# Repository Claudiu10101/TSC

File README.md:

## 1. Descrierea Detaliată a Funcționalității Hardware

Sistemul este un ceas inteligent (smartwatch) cu consum ultra-redus de energie, bazat pe SoC-ul **nRF52840**, care integrează conectivitate Bluetooth Low Energy (BLE) și un afișaj de tip E-Paper (E-Ink).

### Module și Componente Cheie:
* **Unitatea Centrală (MCU):** **nRF52840** (Cortex-M4F la 64MHz). Este ales pentru suportul hardware de Floating Point (necesar procesării datelor de la senzori) și pentru managementul avansat al energiei.
* **Afișajul (E-Paper):** Spre deosebire de ecranele LCD/OLED, acesta consumă energie **doar la schimbarea imaginii**. Circuitul de control (E-Paper Drive) utilizează un convertor boost format din inductorul **L5 (68µH)** și diodele **MBR0530** pentru a genera tensiunile de ±15V necesare orientării particulelor de pigment din ecran.
* **Managementul Bateriei (Power Management):**
    * **Charger (BQ25180):** Permite încărcarea controlată prin USB și monitorizarea prin I2C.
    * **Fuel Gauge (MAX17048):** Folosește algoritmul *ModelGauge* pentru a estima procentul bateriei fără a necesita un rezistor de descărcare (shunt), economisind energie.
    * **Regulator Buck-Boost (RT6160):** Menține constantă tensiunea de 3.3V chiar și când bateria scade sub acest prag (până la 2.5V), maximizând timpul de utilizare.
* **Senzori și Feedback:**
    * **Accelerometru (BMA423):** Include funcții hardware pentru numărarea pașilor (pedometer) și detectarea gestului de "ridicare mână" (tilt-to-wake), trimițând o întrerupere către MCU pentru a-l trezi din sleep.
    * **Haptic Driver (DRV2605):** Permite generarea de efecte de vibrație complexe (peste 100 de librării incluse) pentru notificări discrete.

### Specificații de Comunicație:
* **I2C (Inter-Integrated Circuit):** Lucrează la 400kHz (Fast Mode). Conectează Charger-ul, Fuel Gauge-ul, IMU-ul și Haptic Driver-ul. Această magistrală este ideală pentru senzori datorită simplității și consumului redus.
* **SPI (Serial Peripheral Interface):** Folosit exclusiv pentru ecranul E-Paper pentru a asigura o rată de transfer a datelor suficient de mare pentru refresh-ul imaginii.

---

## 2. Diagrama bloc

```mermaid
graph TD
    %% -- Nodul Central (Microcontroller) --
    subgraph MCU_Block ["Nucleu Central"]
        nRF52840["nRF52840 SoC (Bluetooth 5 / RF)"]
    end

    %% -- Modulul Power Management --
    subgraph Power_Block ["Management Alimentare"]
        LiPo_Batt(("Baterie LiPo 3.7V"))
        USBC_Conn["Conector USB-C (Alimentare/Date)"]
        Charger_BQ["BQ25180 Charger IC"]
        Fuel_MAX["MAX17048 Fuel Gauge"]
        Reg_RT["RT6160 Buck-Boost Regulator"]
    end

    %% -- Modulul Afișaj --
    subgraph Display_Block ["Interfață Vizuală"]
        FPC_Conn["Conector FPC 24p"]
        EPD_Driver["Circuit Comandă E-Paper"]
        EPD_Screen["Ecran E-Paper (E-Ink)"]
    end

    %% -- Modulul Senzori & Feedback --
    subgraph Sensor_Feedback_Block ["Senzori și Actuatori"]
        IMU_BMA["BMA423 Accelerometru"]
        Haptic_DRV["DRV2605 Haptic Driver"]
        Haptic_Mot(("Motor Vibrații"))
    end

    %% -- Linii de Alimentare --
    USBC_Conn ==> Charger_BQ
    LiPo_Batt <==> Charger_BQ
    LiPo_Batt -.-> Fuel_MAX
    Charger_BQ ==> Reg_RT
    Reg_RT ==> nRF52840
    Reg_RT ==> IMU_BMA
    Reg_RT ==> FPC_Conn
    Reg_RT ==> Haptic_DRV

    %% -- Linii de Date --
    nRF52840 <-->|I2C| Charger_BQ
    nRF52840 <-->|I2C| Fuel_MAX
    nRF52840 <-->|I2C| IMU_BMA
    nRF52840 <-->|I2C| Haptic_DRV
    nRF52840 -->|SPI| FPC_Conn
    FPC_Conn <--> EPD_Driver
    EPD_Driver ==> EPD_Screen
```

## 3. Configurarea Pinilor nRF52840 (Pinout Mapping)

Alegerea pinilor pe nRF52840 este critică pentru a evita interferențele și pentru a optimiza rutarea semnalelor RF.

| Pin MCU | Funcție Schematic | Explicație și Justificare |
| :--- | :--- | :--- |
| **P0.26 / P0.27** | **SDA / SCL** | **Magistrala I2C.** Sunt pini digitali generali. S-au ales acești pini pentru a păstra magistrala de senzori grupată fizic pe PCB. |
| **P1.01** | **EPD_BUSY** | **Intrare digitală.** MCU citește acest pin pentru a ști când ecranul a terminat operațiunea de refresh (activ high). |
| **P1.02** | **EPD_RES** | **Reset ecran.** Pin digital folosit pentru inițializarea hardware a controlerului de display. |
| **P1.03** | **EPD_DC** | **Data/Command.** Semnal de control SPI care indică dacă datele trimise sunt comenzi sau pixeli. |
| **P1.04** | **EPD_CS** | **Chip Select.** Activează comunicația SPI cu ecranul. |
| **P1.05** | **EPD_SCK** | **SPI Clock.** Generat de MCU pentru sincronizarea datelor către ecran. |
| **P1.06** | **EPD_MOSI** | **Master Out Slave In.** Linia principală de date către afișaj. |
| **P0.11** | **INT_IMU** | **Intrare Întrerupere.** Conectat la pinul INT1 al BMA423. Trezește procesorul din modul System OFF la detectarea mișcării. |
| **P0.03** | **HAPTIC_EN** | **Trigger.** Activează driverul de vibrații. Poate fi folosit și cu PWM pentru intensitate variabilă. |
| **P0.02, P0.29, P0.31** | **Buttons (UP, ENT, DN)** | **Interfață Utilizator.** Configurați cu Pull-Up intern. Sunt pini capabili de "Sense" pentru a trezi dispozitivul din moduri de consum ultra-redus. |

### Calcule și Considerente de Consum:
1.  **Mod Sleep (Deep Sleep):** Cu nRF52840 în modul *System ON Idle* și senzorii în mod *Low Power*, consumul estimat este de aproximativ **15-20 µA**.
2.  **Refresh Ecran:** În timpul celor 1-2 secunde de refresh E-Paper, consumul sare la **5-10 mA** datorită convertorului boost.
3.  **Baterie:** Folosind o baterie LiPo de 100mAh, cu un management corect al sleep-ului, autonomia poate depăși **2-3 săptămâni**.

Acest design respectă rigurozitatea cerută în cadrul cursului TSC, punând accent pe utilizarea eficientă a perifericelor hardware ale nRF52840 și pe independența modulelor față de CPU prin utilizarea întreruperilor.

### 4. Bill of materials

| Cantitate | Componentă / Modul | Designator (Parts) | Descriere Scurtă | Link Achiziție / Resurse | Datasheet / Link Producător |
| :--- | :--- | :--- | :--- | :--- | :--- |
| 1 | **nRF52840** | U$1 | [cite_start]Microcontroler Bluetooth [cite: 738, 740] | [Mouser/Search](https://www.mouser.com) | [Nordic Semi](https://www.google.com/search?q=https://www.nordicsemi.com) |
| 1 | **2450AT18B100E** | ANT1 | [cite_start]Antenă Chip 2.45GHz [cite: 358, 360] | [cite_start][Arrow Link](https://www.arrow.com/en/products/2450at18b100e/johanson-dielectrics) [cite: 360] | [cite_start][Johanson Tech](https://www.google.com/search?q=https://www.mouser.co.uk/ProductDetail/Johanson-Technology/2450at18b100e) [cite: 364] |
| 1 | **BQ25180YBGR** | IC1 | [cite_start]Charger IC Li-Ion/Polymer [cite: 574, 576] | [cite_start][Mouser Link](https://www.google.com/search?q=https://www.mouser.co.uk/ProductDetail/Texas-Instruments/BQ25180YBGR) [cite: 581] | [cite_start][Texas Instruments](https://www.google.com/search?q=https://www.arrow.com/en/products/bq25180ybgr/texas-instruments) [cite: 576] |
| 1 | **RT6160AWSC** | IC2 | [cite_start]Buck-Boost Regulator [cite: 755, 757] | [cite_start][Mouser Link](https://www.google.com/search?q=https://www.mouser.co.uk/ProductDetail/Richtek/RT6160AWSC) [cite: 762] | [cite_start][Richtek](https://www.google.com/search?q=https://www.mouser.co.uk/ProductDetail/Richtek/RT6160AWSC) [cite: 762] |
| 1 | **BMA423** | IC3 | [cite_start]Accelerometru 3 axe [cite: 559, 561] | [cite_start][Mouser Link](https://www.google.com/search?q=https://www.mouser.co.uk/ProductDetail/Bosch-Sensortec/BMA423) [cite: 566] | [cite_start][Bosch Sensortec](https://www.arrow.com/en/products/bma423/bosch) [cite: 562] |
| 1 | **DRV2605YZFR** | IC4 | [cite_start]Haptic Driver (ERM/LRA) [cite: 604, 606] | [cite_start][Arrow Link](https://www.arrow.com/en/products/drv2605yzfr/texas-instruments) [cite: 606] | [cite_start][Texas Instruments](https://www.arrow.com/en/products/drv2605yzfr/texas-instruments) [cite: 606] |
| 1 | **FTC252012SR47MBCA** | L1 | [cite_start]Inductor 0.47µH [cite: 706, 707] | [cite_start][**JLC Parts (C5832368)**](https://jlcpcb.com/partdetail/6763488-FTC252012SR47MBCA/C5832368) [cite: 712] | [cite_start][TDK](https://jlcpcb.com/partdetail/6763488-FTC252012SR47MBCA/C5832368) [cite: 712] |
| 1 | **KH-TYPE-C-16P** | J2 | [cite_start]Conector USB-C 16 pini [cite: 691, 692] | [cite_start][SnapEDA Link](https://www.snapeda.com/parts/KH-TYPE-C-16P/Kinghelm/view-part/?ref=snap) [cite: 703] | [cite_start][Kinghelm](https://www.snapeda.com/parts/KH-TYPE-C-16P/Kinghelm/view-part/?ref=eda) [cite: 694] |
| 1 | **503480-2400** | J1 | [cite_start]Conector FPC 24 pini [cite: 493, 494] | [cite_start][Mouser Link](https://www.google.com/search?q=https://www.mouser.co.uk/ProductDetail/Molex/503480-2400) [cite: 500] | [cite_start][Molex](https://www.google.com/search?q=https://www.mouser.co.uk/ProductDetail/Molex/503480-2400) [cite: 500] |
| 3 | **MBR0530** | D1, D2, D3 | [cite_start]Diodă Schottky 0.5A 30V [cite: 632, 634] | [cite_start][SnapEDA Link](https://www.snapeda.com/parts/MBR0530/Onsemi/view-part/?ref=snap) [cite: 642] | [cite_start][ON Semi](https://www.snapeda.com/parts/MBR0530/Onsemi/view-part/?ref=eda) [cite: 636] |
| 1 | **USBLC6-2SC6Y** | D4 | [cite_start]Protecție ESD SOT-23-6 [cite: 619, 621] | [cite_start][SnapEDA Link](https://www.snapeda.com/parts/USBLC6-2SC6Y/STMicroelectronics/view-part/?ref=snap) [cite: 629] | [cite_start][STMicro](https://www.snapeda.com/parts/USBLC6-2SC6Y/STMicroelectronics/view-part/?ref=eda) [cite: 622] |
| 1 | **SI1308EDL-T1-GE3** | Q1 | [cite_start]MOSFET N-Ch 30V 1.5A [cite: 646, 647] | [cite_start][SnapEDA Link](https://www.snapeda.com/parts/SI1308EDL-T1-GE3/Vishay+Siliconix/view-part/?ref=snap) [cite: 656] | [cite_start][Vishay](https://www.snapeda.com/parts/SI1308EDL-T1-GE3/Vishay+Siliconix/view-part/?ref=eda) [cite: 648] |
| 3 | **EVP-AKE31A** | SW1-SW3 | [cite_start]Întrerupător (Switch) [cite: 326, 327] | [Panasonic Search](https://www.mouser.com) | [Panasonic](https://www.mouser.com) |
| 1 | **TC2030-IDC** | J3 | [cite_start]Adaptor programare 6 pini [cite: 770, 771] | [Tag-Connect](https://www.tag-connect.com) | [cite_start][Tag-Connect](https://www.tag-connect.com) [cite: 776] |

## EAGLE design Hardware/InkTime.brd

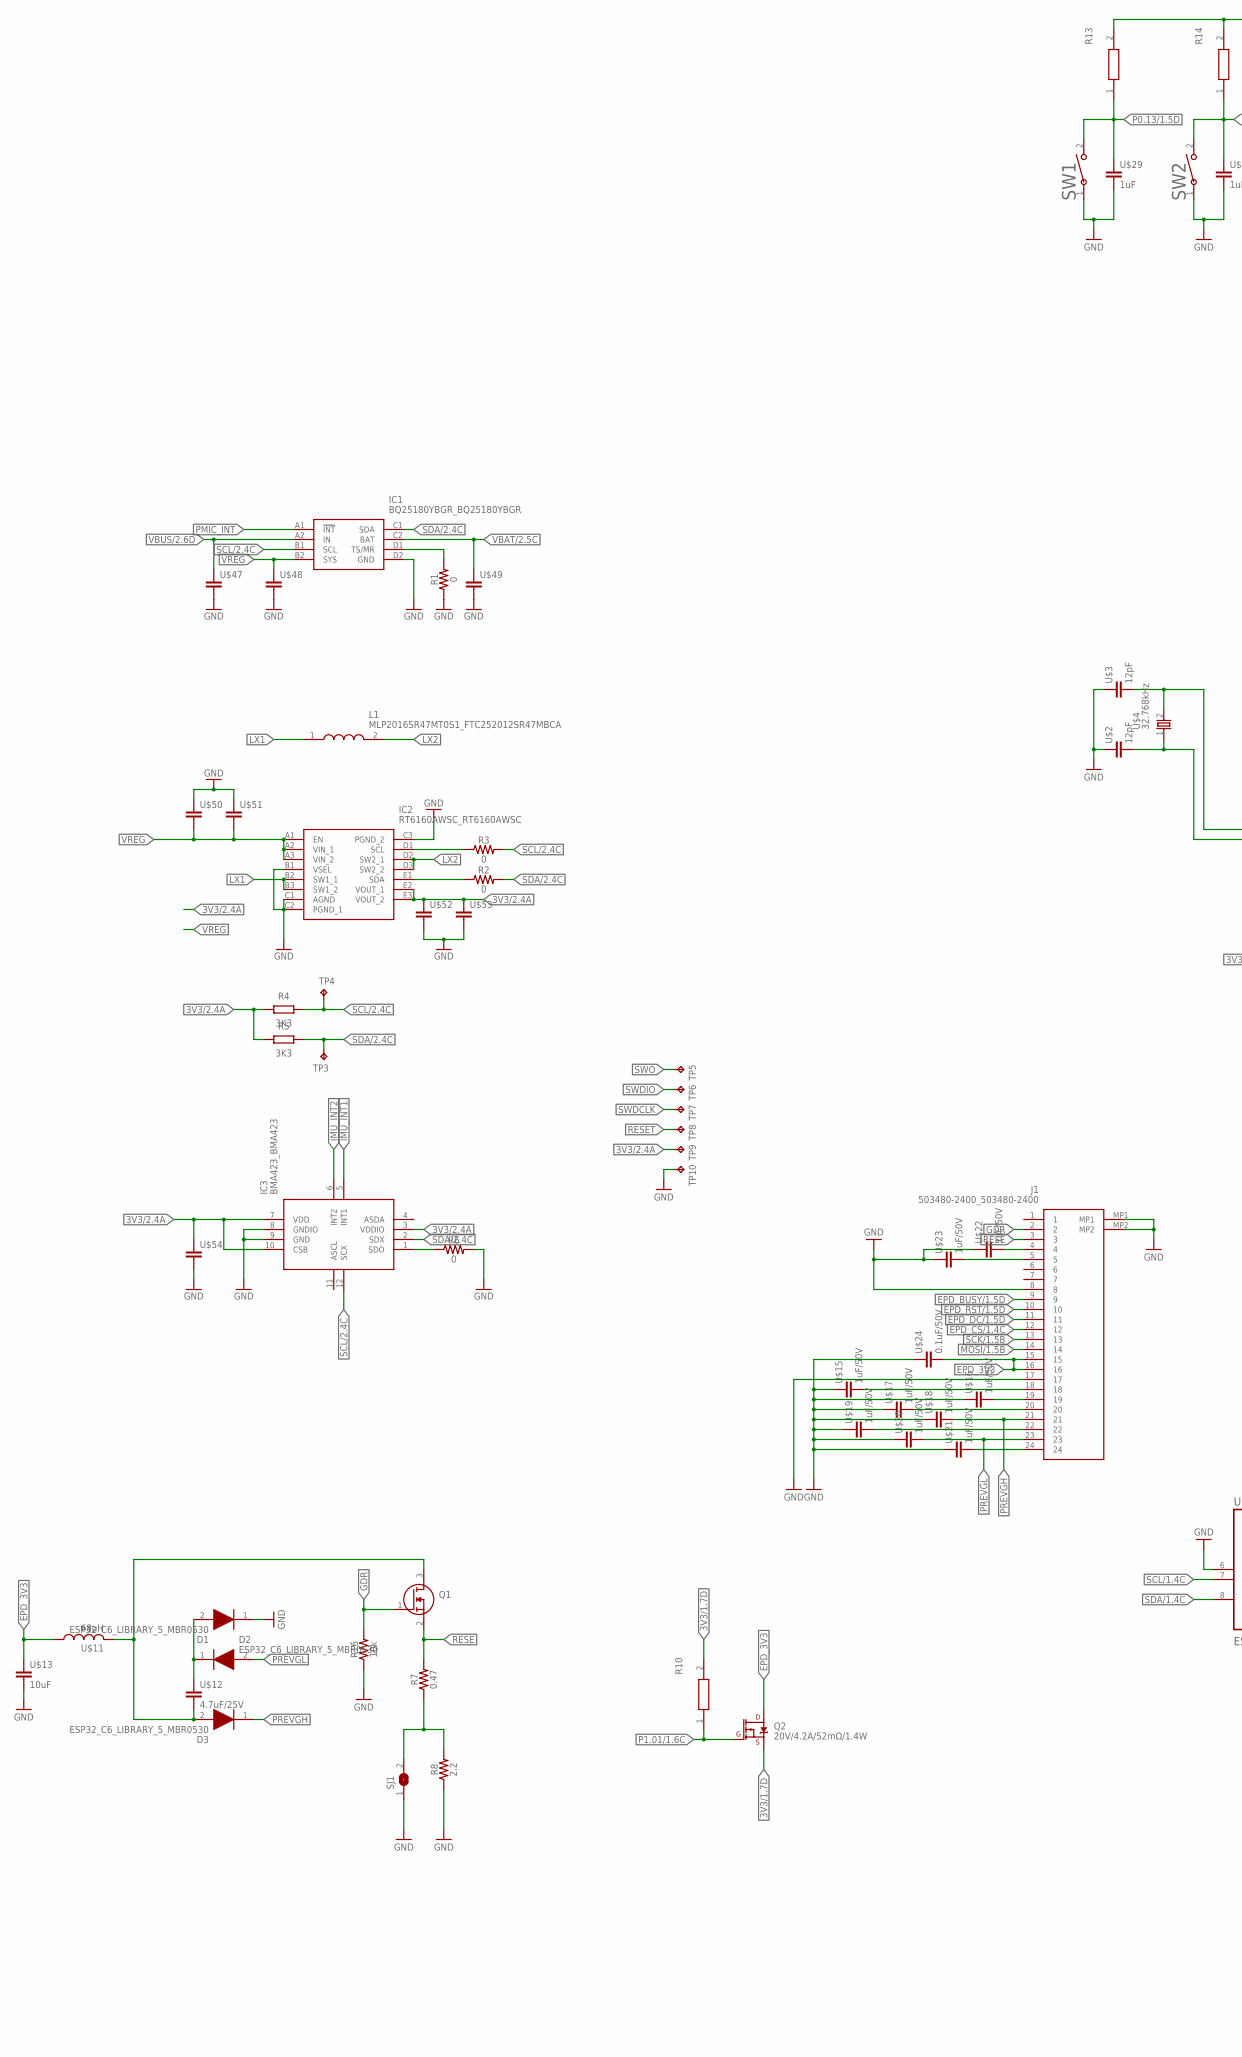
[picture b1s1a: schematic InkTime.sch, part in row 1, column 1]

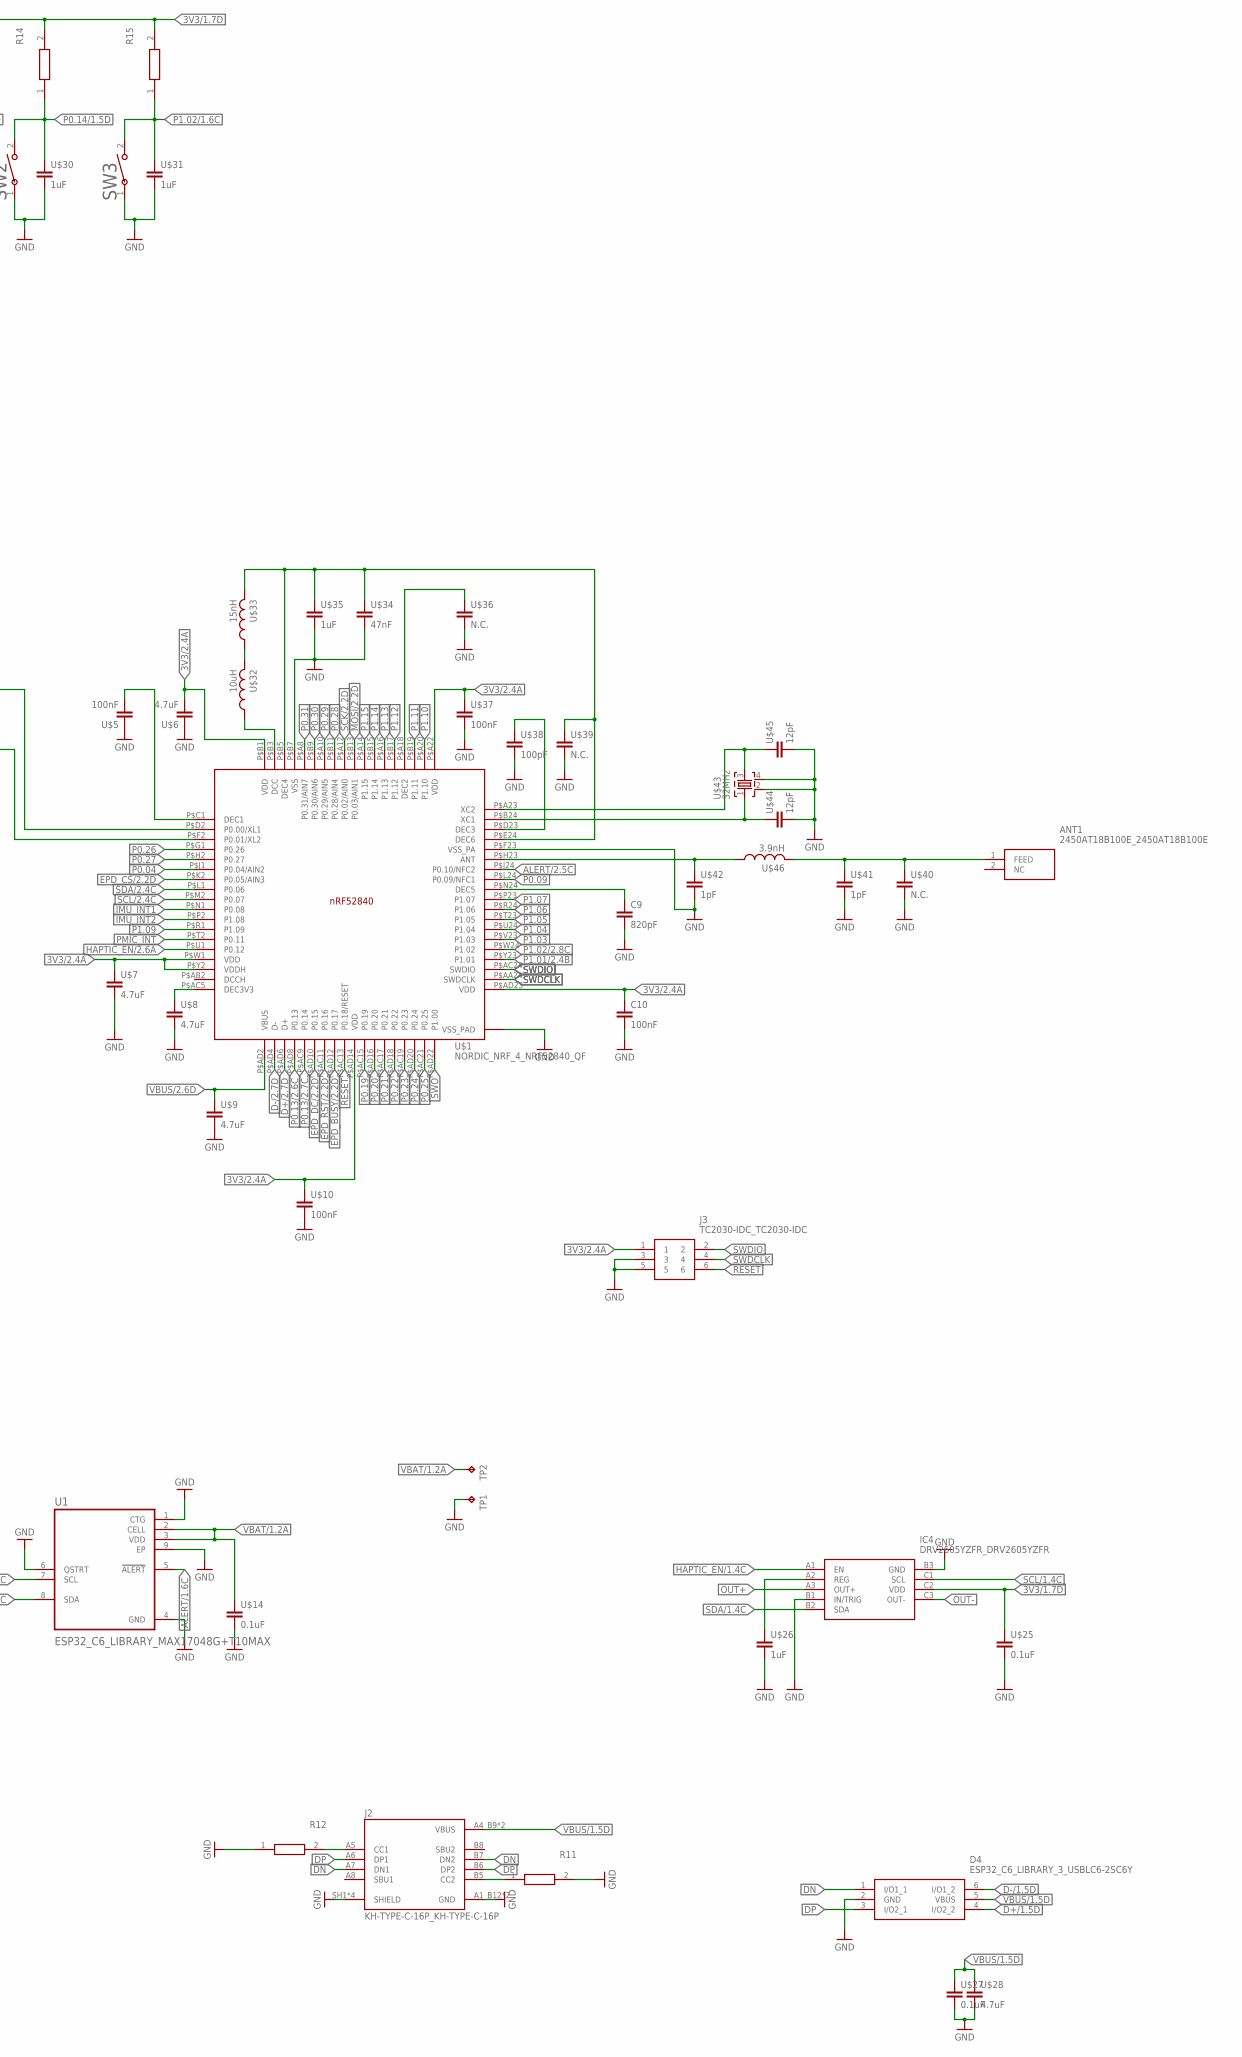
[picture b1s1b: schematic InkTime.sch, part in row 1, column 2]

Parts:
ANT1: 2450AT18B100E_2450AT18B100E; 2450AT18B100E_ANTC3216X140N
C9: 820pF; PERFECT_0402_0402
C10: 100nF; PERFECT_0402_0402
D1, D2, D3: ESP32_C6_LIBRARY_5_MBR0530; ESP32_C6_LIBRARY_5_SOD3716X135N
D4: ESP32_C6_LIBRARY_3_USBLC6-2SC6Y; ESP32_C6_LIBRARY_3_SOT95P280X145-6N
IC1: BQ25180YBGR_BQ25180YBGR; BQ25180YBGR_BGA8C40P2X4_100X155X50
IC2: RT6160AWSC_RT6160AWSC; RT6160AWSC_BGA15C40P3X5_140X230X60
IC3: BMA423_BMA423
IC4: DRV2605YZFR_DRV2605YZFR; DRV2605YZFR_BGA9C50P3X3_144X144X62
J1: 503480-2400_503480-2400; 503480-2400_5034802400
J2: KH-TYPE-C-16P_KH-TYPE-C-16P; KH-TYPE-C-16P_KINGHELM_KH-TYPE-C-16P
J3: TC2030-IDC_TC2030-IDC; TC2030-IDC_TC2030IDC
L1: MLP2016SR47MT0S1_FTC252012SR47MBCA; MLP2016SR47MT0S1_INDC2016X100N
Q1: ESP32_C6_LIBRARY_6_SI1308EDL-T1-GE3; ESP32_C6_LIBRARY_6_SOT65P210X110-3N
Q2: 20V/4.2A/52mΩ/1.4W; ESP32_C6_LIBRARY_4_ESP32_C6_LIBRARY_4_ESP32_C6_LIBRARY_4_ES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
R1, R2, R3, R6: 0; 0603
R4, R5: 3K3; RESC1005X40
R7: 0.47; 0603
R8: 2.2; 0603
R10, R11, R13, R14, R15: CPF0201D7K68C1_CPF0201D7K68C1; CPF0201D7K68C1_0201
R12: 5k1; CPF0201D7K68C1_0201
R16: 10k; 0603
SJ1: ESP32_C6_LIBRARY_7_JUMPER_SJ
SW1, SW2, SW3: 2025-10-22_07-23-44_LIBRARY_EVP-AKE31AEVP-AKE31A; 2025-10-22_07-23-44_LIBRARY_SW_EVP-AKE31A_PAN
TP1, TP2, TP3, TP4, TP5, TP6, TP7, TP8, TP9, TP10: HECTOR_WATCH_1_TPTP20R; HECTOR_WATCH_1_TP20R
U1: ESP32_C6_LIBRARY_MAX17048G+T10MAX; ESP32_C6_LIBRARY_SON50P200X200X80-9N
U$1: NORDIC_NRF_4_NRF52840_QF; NORDIC_NRF_4_AQFN50P700X700X85_HS-74N
U$2, U$3, U$44, U$45: 12pF; NORDIC_NRF_3_RESC0201_L
U$4: 32.768kHz; NORDIC_NRF_1_XTAL_3215_N
U$5, U$10, U$37: 100nF; NORDIC_NRF_3_RESC0201_L
U$6, U$7, U$8, U$9, U$28: 4.7uF; NORDIC_NRF_3_RESC0201_L
U$11: 68uH; NORDIC_NRF_2_RESC0402_L
U$12: 4.7uF/25V; NORDIC_NRF_3_RESC0201_L
U$13: 10uF; NORDIC_NRF_3_RESC0201_L
U$14, U$25, U$27: 0.1uF; NORDIC_NRF_3_RESC0201_L
U$15, U$16, U$17, U$18, U$19, U$20, U$21, U$22, U$23: 1uF/50V; NORDIC_NRF_3_RESC0201_L
U$24: 0.1uF/50V; NORDIC_NRF_3_RESC0201_L
U$26, U$29, U$30, U$31, U$35: 1uF; NORDIC_NRF_3_RESC0201_L
U$32: 10uH; NORDIC_NRF_2_RESC0402_L
U$33: 15nH; NORDIC_NRF_2_RESC0402_L
U$34: 47nF; NORDIC_NRF_3_RESC0201_L
U$36, U$39, U$40: N.C.; NORDIC_NRF_3_RESC0201_L
U$38: 100pF; NORDIC_NRF_3_RESC0201_L
U$41, U$42: 1pF; NORDIC_NRF_3_RESC0201_L
U$43: 32MHz; NORDIC_NRF_BT-XTAL_2016_N
U$46: 3.9nH; NORDIC_NRF_2_RESC0402_L
U$47, U$48, U$49, U$50, U$51, U$52, U$53, U$54: NORDIC_NRF_3_CAPACITOR_0201_L; NORDIC_NRF_3_RESC0201_L

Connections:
3V3/1.7D: IC4.C2 (VDD), Q2.2 (S), R10.2, R13.2, R14.2, R15.2, U$25.1
3V3/2.4A: C10.1, IC2.E2 (VOUT_1), IC2.E3 (VOUT_2), IC3.3 (VDDIO), IC3.7 (VDD), IC3.10 (CSB), J3.1, R4.1, R5.1, TP9.TP, U$1.P$A22 (VDD), U$1.P$AD14 (VDD), U$1.P$AD23 (VDD), U$1.P$B1 (VDD), U$1.P$W1 (VDD), U$1.P$Y2 (VDDH), U$6.2, U$7.1, U$10.1, U$37.1, U$52.1, U$53.1, U$54.1
ALERT/1.6C: U1.5 (!ALERT)
ALERT/2.5C: U$1.P$J24 (P0.10/NFC2)
D+/1.5D: D4.4 (I/O2_2)
D+/2.7D: U$1.P$AD6 (D+)
D-/1.5D: D4.6 (I/O1_2)
D-/2.7D: U$1.P$AD4 (D-)
DN: D4.1 (I/O1_1), J2.A7 (DN1), J2.B7 (DN2)
DP: D4.3 (I/O2_1), J2.A6 (DP1), J2.B6 (DP2)
EPD_3V3: J1.15, J1.16, Q2.3 (D), U$11.1, U$13.1, U$24.2
EPD_BUSY/1.5D: J1.9
EPD_BUSY/2.2D: U$1.P$AD12 (P0.17)
EPD_CS/1.4C: J1.12
EPD_CS/2.2D: U$1.P$K2 (P0.05/AIN3)
EPD_DC/1.5D: J1.11
EPD_DC/2.2D: U$1.P$AD10 (P0.15)
EPD_RST/1.5D: J1.10
EPD_RST/2.2D: U$1.P$AC11 (P0.16)
GDR: J1.2, Q1.1 (G), R16.2
GND: C9.2, C10.2, D1.1 (K), D4.2 (GND), IC1.D2 (GND), IC2.B1 (VSEL), IC2.C1 (AGND), IC2.C2 (PGND_1), IC2.C3 (PGND_2), IC3.8 (GNDIO), IC3.9 (GND), IC4.B1 (IN/TRIG), IC4.B3 (GND), J1.8, J1.17, J1.MP1, J1.MP2, J2.A1_B12 (GND), J2.A12_B1 (GND), J2.SH1 (SHIELD), J2.SH2 (SHIELD), J2.SH3 (SHIELD), J2.SH4 (SHIELD), J3.3, J3.5, R1.1, R6.2, R8.1, R11.2, R12.1, R16.1, SJ1.1, SW1.1, SW2.1, SW3.1, TP1.TP, TP10.TP, U1.1 (CTG), U1.4 (GND), U1.6 (QSTRT), U1.9 (EP), U$1.P$74 (VSS_PAD), U$1.P$75 (VSS_PAD), U$1.P$76 (VSS_PAD), U$1.P$77 (VSS_PAD), U$1.P$78 (VSS_PAD), U$1.P$79 (VSS_PAD), U$1.P$80 (VSS_PAD), U$1.P$81 (VSS_PAD), U$1.P$82 (VSS_PAD), U$1.P$83 (VSS_PAD), U$1.P$84 (VSS_PAD), U$1.P$85 (VSS_PAD), U$1.P$86 (VSS_PAD), U$1.P$87 (VSS_PAD), U$1.P$88 (VSS_PAD), U$1.P$89 (VSS_PAD), U$1.P$90 (VSS_PAD), U$1.P$B7 (VSS), U$1.P$F23 (VSS_PA), U$2.1, U$3.1, U$5.1, U$6.1, U$7.2, U$8.2, U$9.2, U$10.2, U$13.2, U$14.2, U$15.1, U$16.1, U$17.1, U$18.1, U$19.1, U$20.1, U$21.1, U$22.1, U$23.1, U$24.1, U$25.2, U$26.2, U$27.2, U$28.2, U$29.2, U$30.2, U$31.2, U$34.2, U$35.2, U$36.2, U$37.2, U$38.2, U$39.2, U$40.2, U$41.2, U$42.2, U$43.2, U$43.4, U$44.2, U$45.2, U$47.2, U$48.2, U$49.2, U$50.1, U$51.1, U$52.2, U$53.2, U$54.2
HAPTIC_EN/1.4C: IC4.A1 (EN)
HAPTIC_EN/2.6A: U$1.P$U1 (P0.12)
IMU_INT1: IC3.5 (INT1), U$1.P$N1 (P0.08)
IMU_INT2: IC3.6 (INT2), U$1.P$P2 (P1.08)
LX1: IC2.B2 (SW1_1), IC2.B3 (SW1_2), L1.1
LX2: IC2.D2 (SW2_1), IC2.D3 (SW2_2), L1.2
MOSI/1.5B: J1.14
MOSI/2.2D: U$1.P$B13 (P0.03/AIN1)
unnamed: U$1.P$AC5 (DEC3V3), U$8.1
unnamed: J2.A5 (CC1), R12.2
unnamed: D3.2 (A), Q1.3 (D), U$11.2, U$12.2
unnamed: IC2.D1 (SCL), R3.1
unnamed: IC3.1 (SDO), R6.1
unnamed: IC1.D1 (TS/MR), R1.2
unnamed: IC2.E1 (SDA), R2.1
unnamed: U$1.P$D2 (P0.00/XL1), U$3.2, U$4.2
unnamed: U$1.P$B5 (DEC4), U$1.P$E24 (DEC6), U$33.2, U$34.1, U$35.1, U$39.1
unnamed: U$1.P$B3 (DCC), U$32.1
unnamed: D1.2 (A), D2.1 (K), U$12.1
unnamed: U$32.2, U$33.1
unnamed: J2.B5 (CC2), R11.1
unnamed: R7.1, R8.2, SJ1.2
unnamed: U$1.P$A18 (DEC2), U$36.1
unnamed: U$1.P$A23 (XC2), U$43.3, U$45.1
unnamed: U$1.P$D23 (DEC3), U$38.1
unnamed: IC4.A2 (REG), U$26.1
unnamed: U$1.P$C1 (DEC1), U$5.2
unnamed: U$1.P$F2 (P0.01/XL2), U$2.2, U$4.1
unnamed: U$1.P$H23 (ANT), U$42.1, U$46.1
unnamed: J1.18, U$15.2
unnamed: J1.19, U$16.2
unnamed: J1.20, U$17.2
unnamed: J1.22, U$19.2
unnamed: U$1.P$B24 (XC1), U$43.1, U$44.1
unnamed: J1.24, U$21.2
unnamed: J1.4, U$22.2
unnamed: J1.5, U$23.2
unnamed: ANT1.1 (FEED), U$40.1, U$41.1, U$46.2
unnamed: C9.1, U$1.P$N24 (DEC5)
OUT+: IC4.A3 (OUT+)
OUT-: IC4.C3 (OUT-)
P0.04: U$1.P$J1 (P0.04/AIN2)
P0.09: U$1.P$L24 (P0.09/NFC1)
P0.13/1.5D: R13.1, SW1.2, U$29.1
P0.13/2.6C: U$1.P$AD8 (P0.13)
P0.13/2.7C: U$1.P$AC9 (P0.14)
P0.14/1.5D: R14.1, SW2.2, U$30.1
P0.19: U$1.P$AC15 (P0.19)
P0.20: U$1.P$AD16 (P0.20)
P0.21: U$1.P$AC17 (P0.21)
P0.22: U$1.P$AD18 (P0.22)
P0.23: U$1.P$AC19 (P0.23)
P0.24: U$1.P$AD20 (P0.24)
P0.25: U$1.P$AC21 (P0.25)
P0.26: U$1.P$G1 (P0.26)
P0.27: U$1.P$H2 (P0.27)
P0.28: U$1.P$B11 (P0.28/AIN4)
P0.29: U$1.P$A10 (P0.29/AIN5)
P0.30: U$1.P$B9 (P0.30/AIN6)
P0.31: U$1.P$A8 (P0.31/AIN7)
P1.01/1.6C: Q2.1 (G), R10.1
P1.01/2.4B: U$1.P$Y23 (P1.01)
P1.02/1.6C: R15.1, SW3.2, U$31.1
P1.02/2.8C: U$1.P$W24 (P1.02)
P1.03: U$1.P$V23 (P1.03)
P1.04: U$1.P$U24 (P1.04)
P1.05: U$1.P$T23 (P1.05)
P1.06: U$1.P$R24 (P1.06)
P1.07: U$1.P$P23 (P1.07)
P1.09: U$1.P$R1 (P1.09)
P1.10: U$1.P$A20 (P1.10)
P1.11: U$1.P$B19 (P1.11)
P1.12: U$1.P$B17 (P1.12)
P1.13: U$1.P$A16 (P1.13)
P1.14: U$1.P$B15 (P1.14)
P1.15: U$1.P$A14 (P1.15)
PMIC_INT: IC1.A1 (!INT), U$1.P$T2 (P0.11)
PREVGH: D3.1 (K), J1.21, U$18.2
PREVGL: D2.2 (A), J1.23, U$20.2
RESE: J1.3, Q1.2 (S), R7.2
RESET: J3.6, TP8.TP, U$1.P$AC13 (P0.18/RESET)
SCK/1.5B: J1.13
SCK/2.2D: U$1.P$A12 (P0.02/AIN0)
SCL/1.4C: IC4.C1 (SCL), U1.7 (SCL)
SCL/2.4C: IC1.B1 (SCL), IC3.12 (SCX), R3.2, R4.2, TP4.TP, U$1.P$M2 (P0.07)
SDA/1.4C: IC4.B2 (SDA), U1.8 (SDA)
SDA/2.4C: IC1.C1 (SDA), IC3.2 (SDX), R2.2, R5.2, TP3.TP, U$1.P$L1 (P0.06)
SWDCLK: J3.4, TP7.TP, U$1.P$AA24 (SWDCLK)
SWDIO: J3.2, TP6.TP, U$1.P$AC24 (SWDIO)
SWO: TP5.TP, U$1.P$AD22 (P1.00)
VBAT/1.2A: TP2.TP, U1.2 (CELL), U1.3 (VDD), U$14.1
VBAT/2.5C: IC1.C2 (BAT), U$49.1
VBUS/1.5D: D4.5 (VBUS), J2.A4_B9 (VBUS), J2.A9_B4 (VBUS), U$27.1, U$28.1
VBUS/2.6D: IC1.A2 (IN), U$1.P$AD2 (VBUS), U$9.1, U$47.1
VREG: IC1.B2 (SYS), IC2.A1 (EN), IC2.A2 (VIN_1), IC2.A3 (VIN_2), U$48.1, U$50.2, U$51.2

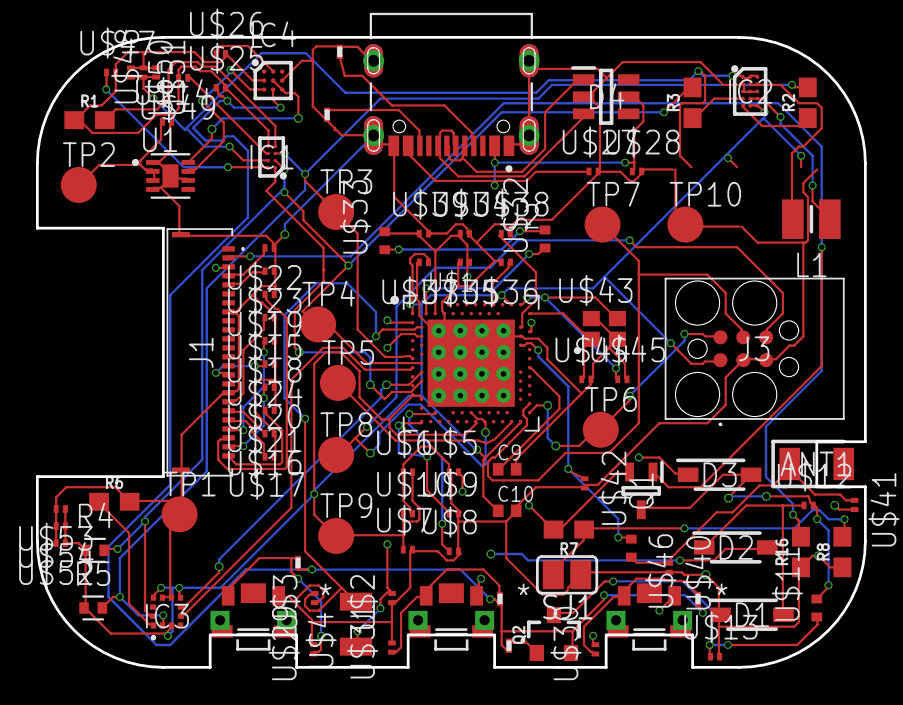
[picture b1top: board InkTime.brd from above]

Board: 4 copper layers, 46.0 x 35.0 mm, 101 parts (0 on the bottom side), 63 nets.

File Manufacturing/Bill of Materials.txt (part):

Partlist exported from Fusion Hub: Alexe   Project: iiytkhgjh  Board: InkTime.fbrd at 4/10/2026 7:06 AM

Qty Value                                            Device                                                                       Package                                                                                                                Parts                                                Description                                                                                                               ARROW_PART_NUMBER ARROW_PRICE-STOCK                                                                                AVAILABILITY CATEGORY  CHECK_PRICES                                                                       DATASHEET DESCRIPTION                                                                                              HEIGHT                                    JLCPCB       MANUFACTURER                                        MANUFACTURER_NAME                                                MANUFACTURER_PART_NUMBER MF                 MOUSER_PART_NUMBER MOUSER_PRICE-STOCK                                                                                           MP                                                                                                       MPN OPERATING_TEMPERATURE PACKAGE                     PACKAGE_SIZE PACKAGE_TYPE  PART_STATUS                  POPULARITY PRICE PROD_ID    PURCHASE-URL                                                                                                                           ROHS SERIES SNAPEDA_LINK                                                                                                                                    SUBCATEGORY TEMPERATURE_COEFFICIENT THERMALLOSS                                                                         TOLERANCE TP_SIGNAL_NAME TYPE VALUE             
1                                                    ESP32_C6_LIBRARY_7_JUMPER_SJ                                                 ESP32_C6_LIBRARY_7_JUMPER_SJ                                                                                           SJ1                                                  SMD solder JUMPER                                                                                                                                                                                                                                                                                                                                                                                                                                                                                                                                                                                                                                                                                                                                                                                                                                                                                                                                                                                                                                        3                                                                                                                                                                                                                                                                                                                                                                                                                                                                                                      
8                                                    NORDIC_NRF_3_CAPACITOR_0201_L                                                NORDIC_NRF_3_RESC0201_L                                                                                                U$47, U$48, U$49, U$50, U$51, U$52, U$53, U$54       Generic chip capacitor                                                                                                                                                                                                                                                                                                                                                                                                                                                                                                                                                                                                                                                                                                                                                                                                                                                                                                                                                                                                                                                                                                                                                                                                                                                                                                                                                                                                                                                                                                                                          
4   0                                                0OHM-0603-1/10W                                                              0603                                                                                                                   R1, R2, R3, R6                                       0O resistor                                                                                                                                                                                                                                                                                                                                                                                                                                                                                                                                                                                                                                                                                                                                                                                                                                                                                                                                                                                                                                                               RES-08609                                                                                                                                                                                                                                                                                                                                                                                                                                                           0                 
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
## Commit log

2026-04-10 stuff
2026-04-10 diagram
2026-04-10 Refactor Mermaid diagram for hardware components
    Updated the Mermaid diagram in README.md to improve clarity and structure.

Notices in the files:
parts and their libraries:
SparkFun-Resistors: Licensing: Creative Commons ShareAlike 4.0 International - https://creativecommons.org/licenses/by-sa/4.0
